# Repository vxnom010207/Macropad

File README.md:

# HACKPAD
This project is a custom 6-key mechanical macropad designed for productivity and workflow automation.
#  Softwares Used
1. Autodesk Fusion
2. KiCad 9.0
3. Mu Editor

## Components Used
1) Microcontroller - **Seed Studio XIAO RP2040**
2) Switches(x6) - **Cherry MX Compatible Mechanical Switches**
3) RGB LEDs(x4) - **SK6812MINI (3535) Addressable RGB LEDs**
4) Case - 3D printed

## PCB Layout

**Key Pins:** - A0,A1,A2,A3,D4,D5
**RGB** - TX 
**POWER** - 5V VBUSs

## Keymapping
- Key 1 - Vol Up
- Key 2 - Vol Down
- Key 3 - Tap:Mute / Double Tap : Play-Pause
- Key 4 - Alt + Tab ( Tab Switch)
- Key 5 - Win + Ctrl + Left ( Previous desktop)
- Key 6 - Win + Ctrl + Right( Next desktop)

## PCB Schematic and Design

## 3d Model ( Case )

## References 
[HackClub's hackpad tutorial](https://blueprint.hackclub.com/hackpad)

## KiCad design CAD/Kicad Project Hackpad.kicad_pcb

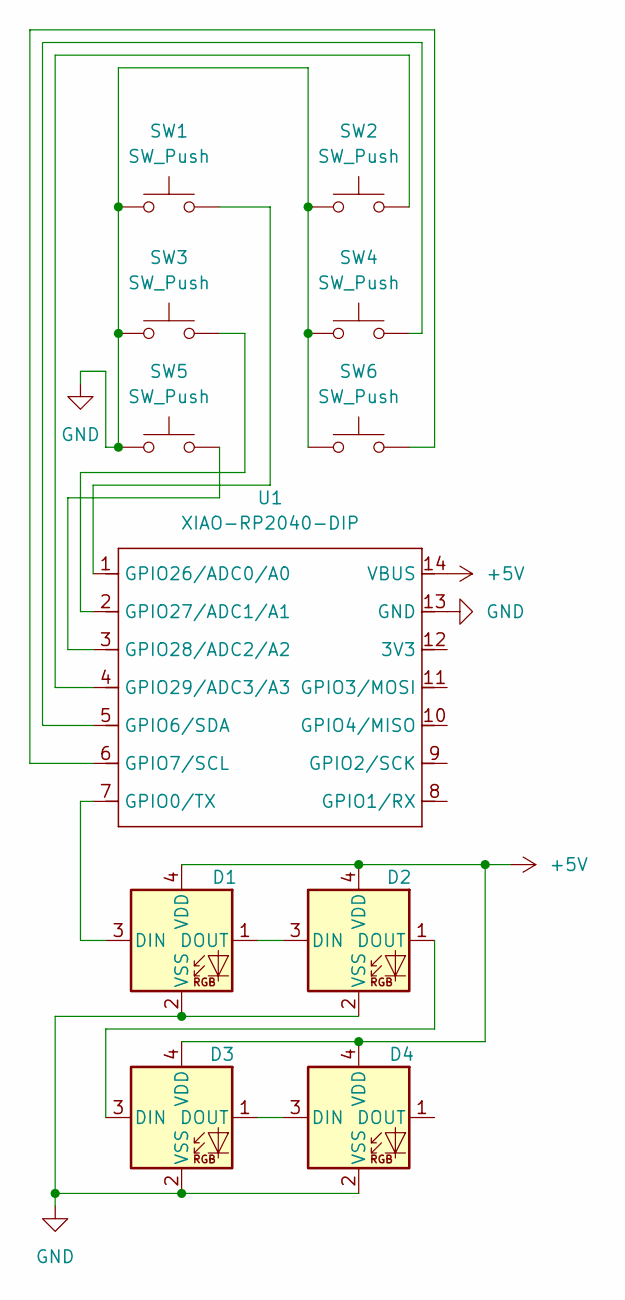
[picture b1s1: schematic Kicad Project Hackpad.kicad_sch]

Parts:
D1, D2, D3, D4: SK6812MINI; LED_SK6812MINI_PLCC4_3.5x3.5mm_P1.75mm
SW1, SW2, SW3, SW4, SW5, SW6: SW_Push; SW_Cherry_MX_1.00u_PCB
U1: XIAO-RP2040-DIP

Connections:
+5V: D1.4 (VDD), D2.4 (VDD), D3.4 (VDD), D4.4 (VDD), U1.14 (VBUS)
GND: D1.2 (VSS), D2.2 (VSS), D3.2 (VSS), D4.2 (VSS), SW1.1, SW2.1, SW3.1, SW4.1, SW5.1, SW6.1, U1.13 (GND)
unnamed: D1.3 (DIN), U1.7 (GPIO0/TX)
unnamed: D1.1 (DOUT), D2.3 (DIN)
unnamed: D2.1 (DOUT), D3.3 (DIN)
unnamed: D3.1 (DOUT), D4.3 (DIN)
unnamed: SW4.2, U1.5 (GPIO6/SDA)
unnamed: SW6.2, U1.6 (GPIO7/SCL)
unnamed: SW1.2, U1.1 (GPIO26/ADC0/A0)
unnamed: SW3.2, U1.2 (GPIO27/ADC1/A1)
unnamed: SW5.2, U1.3 (GPIO28/ADC2/A2)
unnamed: SW2.2, U1.4 (GPIO29/ADC3/A3)

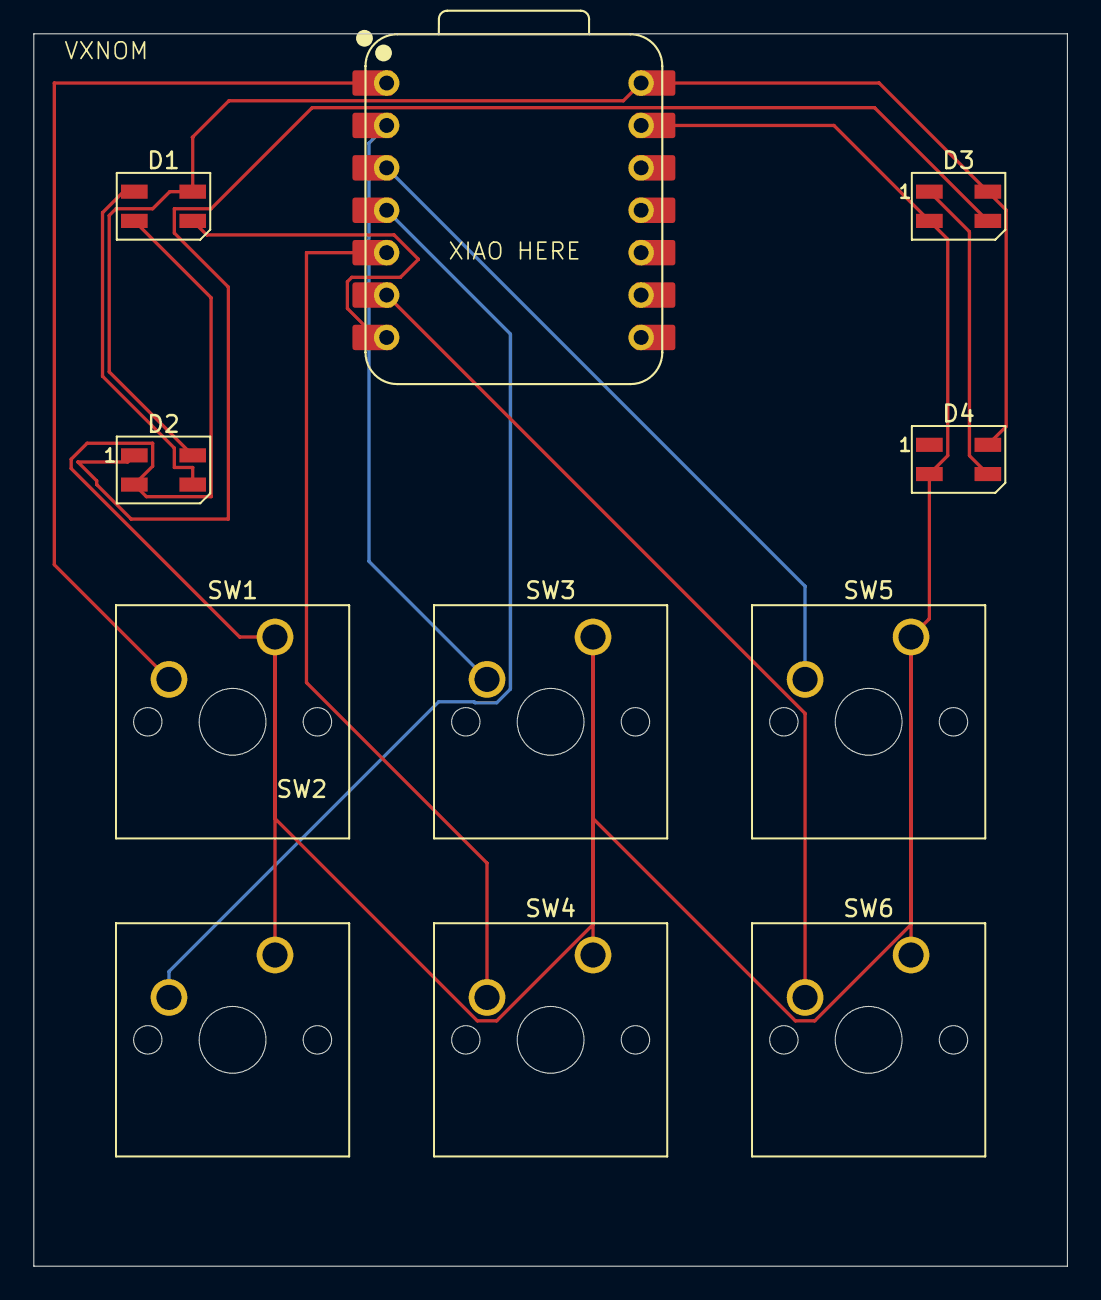
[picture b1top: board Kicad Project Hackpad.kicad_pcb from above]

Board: 2 copper layers, 61.9 x 73.8 mm, 11 parts (0 on the bottom side), 12 nets.

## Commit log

2025-12-26 Update readme
    added detailed specifications.
